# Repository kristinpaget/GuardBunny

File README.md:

# GuardBunny
## An active RFID shield

**tl;dr: Send the contents of the "Manufacturing" folder to any PCBA shop and they should be able to make you a batch of GuardBunnies.**

In this repository:

- Eagle Files:

Schematic, PCB layout, and library for the counter chip.  Built with Eagle for Mac 7.5.0.

- Logo

GuardBunny logo design

- Manufacturing

Gerber files (including Excellon drill data), Bill of Materials, component placement co-ordinates.

- Presentation

The slides.  Link to follow to video of the talk.

- schematic.png

Exactly what it says on the tin :D

If you would be interested in joining a group order for GuardBunnies, send me an email at iwantabunny@tombom.co.uk and tell me how many you'd like - bear in mind they'll be $15-20 each unless we can get some quantity going.

Released under Creative Commons license Attribution-ShareAlike 4.0 International (CC BY-SA 4.0) - http://creativecommons.org/licenses/by-sa/4.0/

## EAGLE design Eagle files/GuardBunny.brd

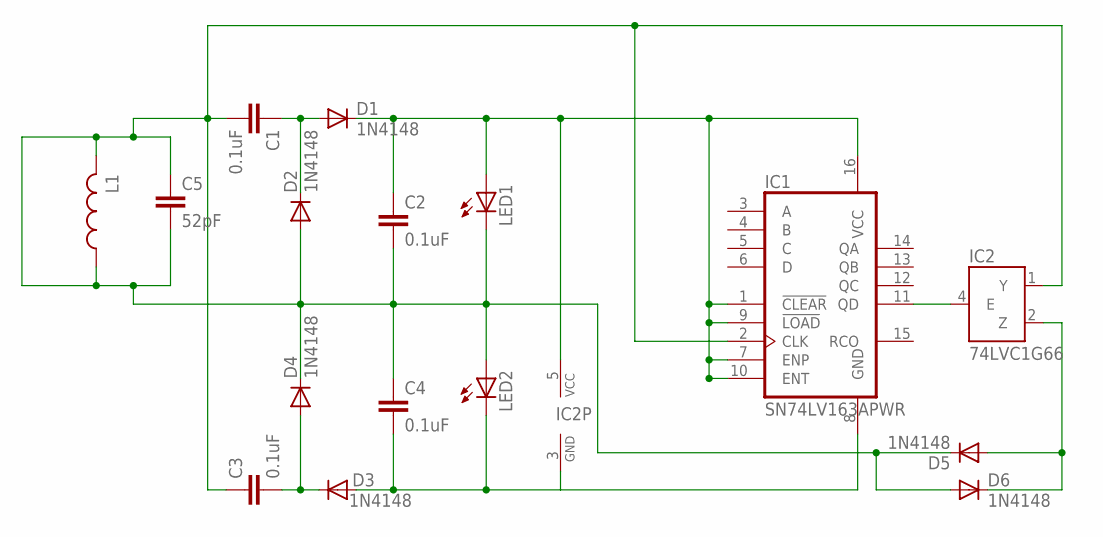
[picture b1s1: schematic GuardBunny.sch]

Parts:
C1, C2, C3, C4: 0.1uF; C0603
C5: 52pF; C0603
D1, D2, D3, D4, D5, D6: 1N4148; SOD523
IC1: SN74LV163APWR; TSSOP16
IC2: 74LVC1G66; SOT23-5
L1: L-USL2012C; L2012C
LED1, LED2: LEDCHIP-LED0603; CHIP-LED0603

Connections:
GND: C4.2, D3.A, IC1.8 (GND), IC2.3 (GND), LED2.C
unnamed: C1.2, C2.2, C3.1, C4.1, C5.1, C5.2, D2.A, D4.C, D5.C, D6.A, IC1.2 (CLK), IC2.1 (Y), L1.1, L1.2, LED1.C, LED2.A
unnamed: C1.1, D1.A, D2.C
unnamed: IC1.11 (QD), IC2.4 (E)
unnamed: C3.2, D3.C, D4.A
unnamed: D5.A, D6.C, IC2.2 (Z)
VCC: C2.1, D1.C, IC1.1 (!CLEAR), IC1.7 (ENP), IC1.9 (!LOAD), IC1.10 (ENT), IC1.16 (VCC), IC2.5 (VCC), LED1.A

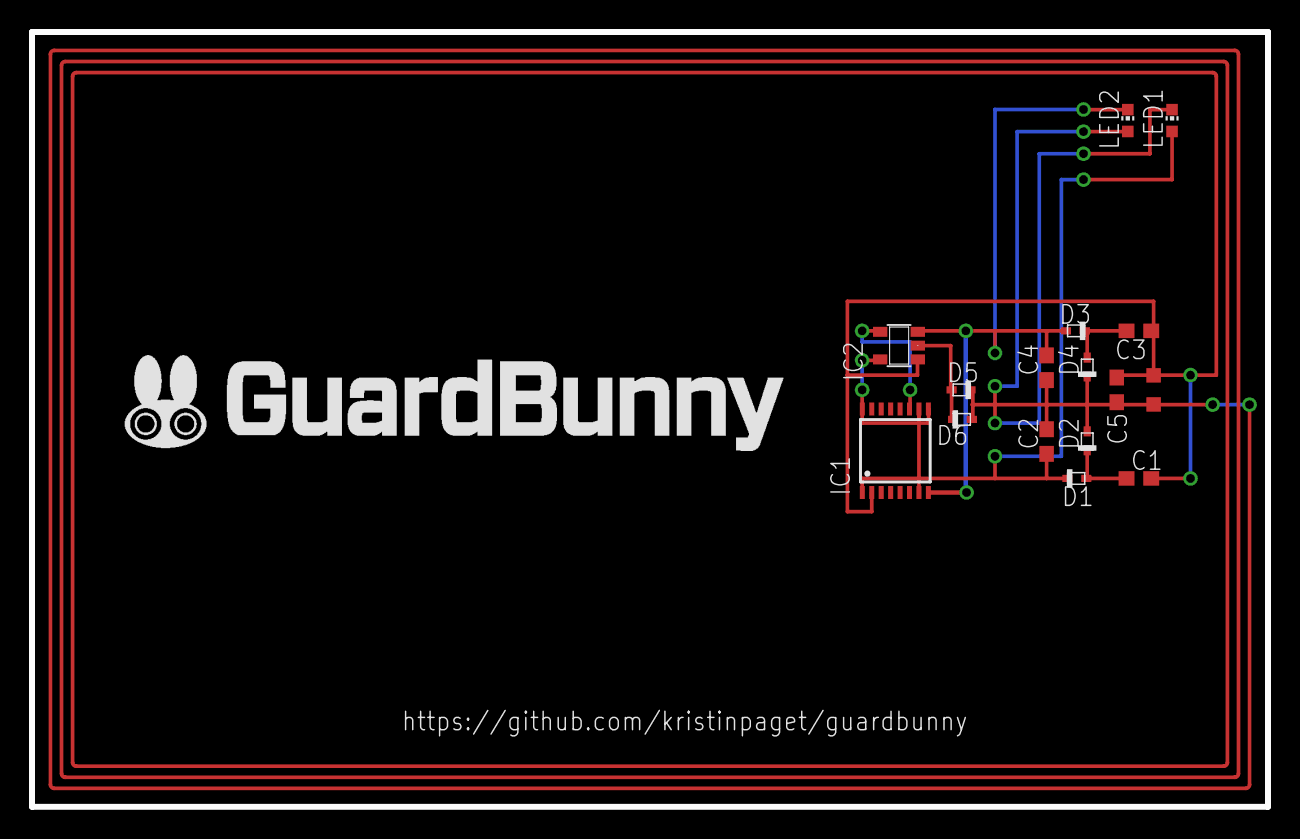
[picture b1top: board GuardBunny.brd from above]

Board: 2 copper layers, 85.1 x 53.3 mm, 16 parts (0 on the bottom side), 7 nets.

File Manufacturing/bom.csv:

Description,Qty,Ref des,MFG P/N,MFG,Mouser P/N
MLCC 0.1uF 25V 0603,4,"C1, C2, C3, C4",VJ0603V104ZXXCW1BC,Vishay,77-VJ0603V104ZXXCBC
MLCC 200pF 100V C0G 0603,1,C5,GRM1885C2A201JA01D,Murata,81-GRM1885C2A201JA1D
Diode 1N4148X,6,"D1, D2, D3, D4, D5, D6",1N4148X-TP,MCC,833-1N4148X-TP
74LV163 4-bit counter,1,IC1,SN74LV163APWR,TI,595-SN74LV163APWR
74LVC1G66 analog switch,1,IC2,SN74LVC1G66DBVR,TI,595-SN74LVC1G66DBVR
DNP,1,L1,DNP,DNP,DNP
RED LED,2,"LED1, LED2",LS Q976-NR-1,OSRAM,720-LSQ976-NR-1
